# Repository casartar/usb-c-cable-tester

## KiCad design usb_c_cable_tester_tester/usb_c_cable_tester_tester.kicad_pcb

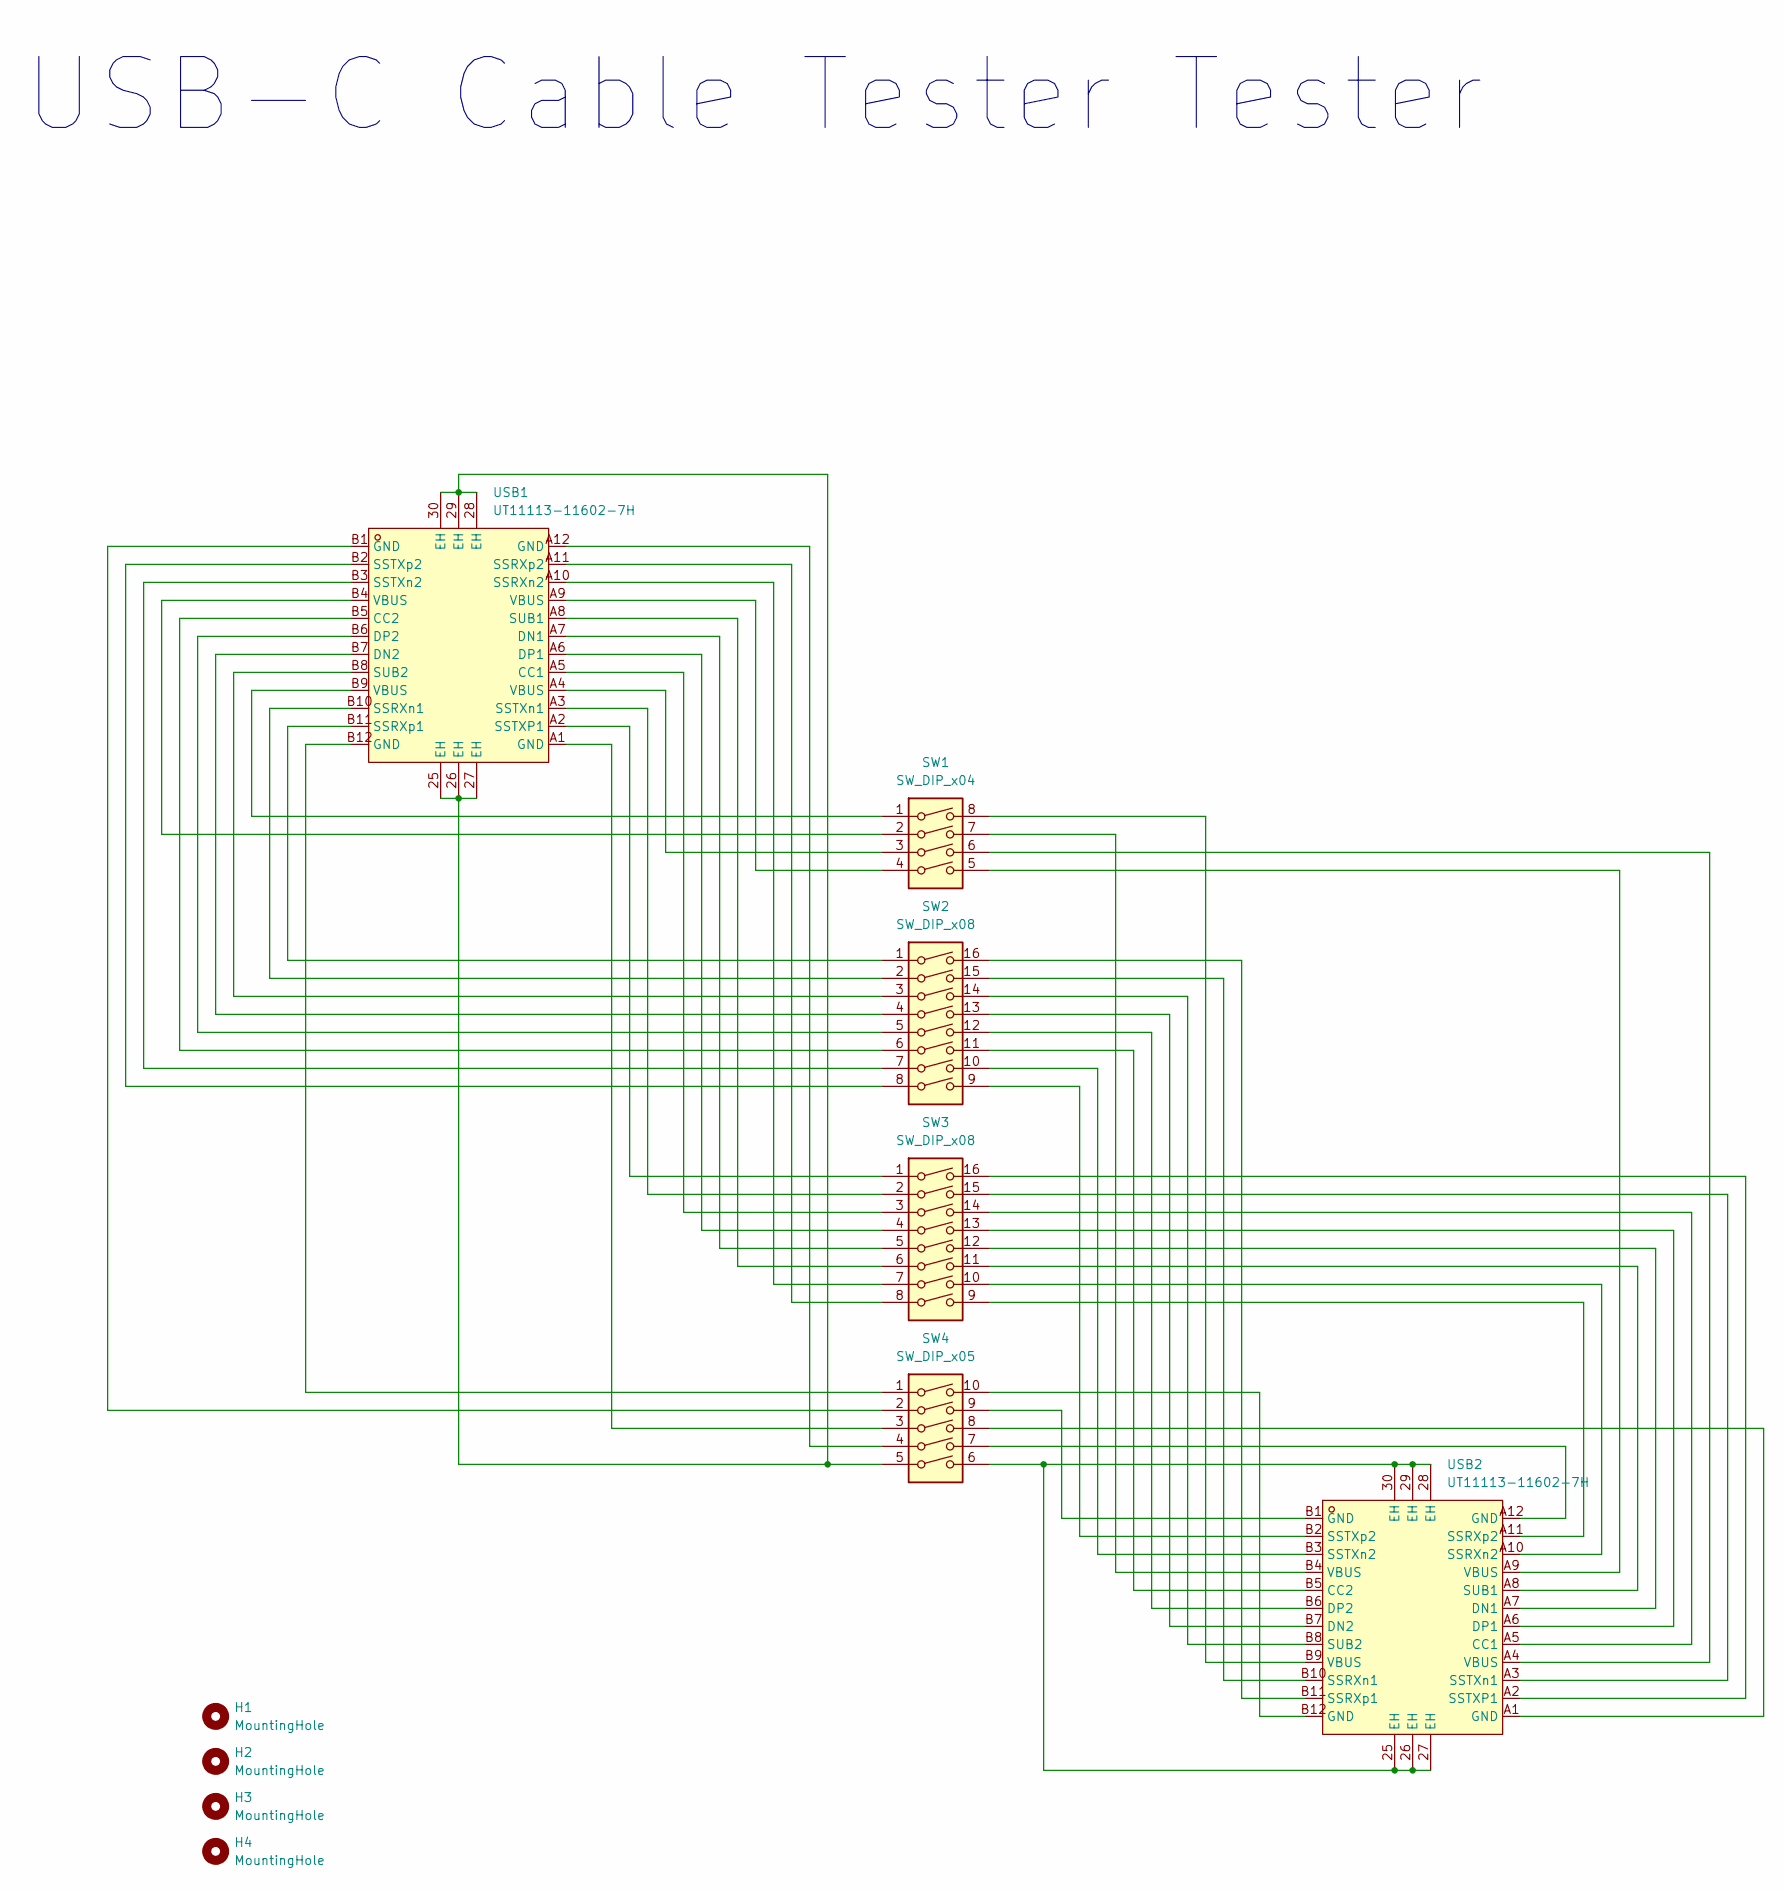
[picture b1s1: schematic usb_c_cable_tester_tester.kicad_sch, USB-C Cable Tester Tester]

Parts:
H1, H2, H3, H4: MountingHole; MountingHole_3.2mm_M3
SW1: SW_DIP_x04; SW_DIP_SPSTx04_Slide_9.78x12.34mm_W7.62mm_P2.54mm
SW2, SW3: SW_DIP_x08; SW_DIP_SPSTx08_Slide_9.78x22.5mm_W7.62mm_P2.54mm
SW4: SW_DIP_x05; SW_DIP_SPSTx05_Slide_9.78x14.88mm_W7.62mm_P2.54mm
USB1, USB2: UT11113-11602-7H; USB-C-SMD_UT11113-11602-7H; LCSC Part C2761408

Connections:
unnamed: SW1.1, USB1.B9 (VBUS)
unnamed: SW1.2, USB1.B4 (VBUS)
unnamed: SW1.3, USB1.A4 (VBUS)
unnamed: SW1.4, USB1.A9 (VBUS)
unnamed: SW1.5, USB2.A9 (VBUS)
unnamed: SW1.6, USB2.A4 (VBUS)
unnamed: SW1.7, USB2.B4 (VBUS)
unnamed: SW1.8, USB2.B9 (VBUS)
unnamed: SW4.1, USB1.B12 (GND)
unnamed: SW4.2, USB1.B1 (GND)
unnamed: SW4.3, USB1.A1 (GND)
unnamed: SW4.4, USB1.A12 (GND)
unnamed: SW4.5, USB1.25 (EH), USB1.26 (EH), USB1.27 (EH), USB1.28 (EH), USB1.29 (EH), USB1.30 (EH)
unnamed: SW4.6, USB2.25 (EH), USB2.26 (EH), USB2.27 (EH), USB2.28 (EH), USB2.29 (EH), USB2.30 (EH)
unnamed: SW4.7, USB2.A12 (GND)
unnamed: SW4.8, USB2.A1 (GND)
unnamed: SW4.9, USB2.B1 (GND)
unnamed: SW4.10, USB2.B12 (GND)
unnamed: SW3.3, USB1.A5 (CC1)
unnamed: SW2.6, USB1.B5 (CC2)
unnamed: SW3.5, USB1.A7 (DN1)
unnamed: SW2.4, USB1.B7 (DN2)
unnamed: SW3.4, USB1.A6 (DP1)
unnamed: SW2.5, USB1.B6 (DP2)
unnamed: SW2.2, USB1.B10 (SSRXn1)
unnamed: SW3.7, USB1.A10 (SSRXn2)
unnamed: SW2.1, USB1.B11 (SSRXp1)
unnamed: SW3.8, USB1.A11 (SSRXp2)
unnamed: SW3.1, USB1.A2 (SSTXP1)
unnamed: SW3.2, USB1.A3 (SSTXn1)
unnamed: SW2.7, USB1.B3 (SSTXn2)
unnamed: SW2.8, USB1.B2 (SSTXp2)
unnamed: SW3.6, USB1.A8 (SUB1)
unnamed: SW2.3, USB1.B8 (SUB2)
unnamed: SW3.14, USB2.A5 (CC1)
unnamed: SW2.11, USB2.B5 (CC2)
unnamed: SW3.12, USB2.A7 (DN1)
unnamed: SW2.13, USB2.B7 (DN2)
unnamed: SW3.13, USB2.A6 (DP1)
unnamed: SW2.12, USB2.B6 (DP2)
unnamed: SW2.15, USB2.B10 (SSRXn1)
unnamed: SW3.10, USB2.A10 (SSRXn2)
unnamed: SW2.16, USB2.B11 (SSRXp1)
unnamed: SW3.9, USB2.A11 (SSRXp2)
unnamed: SW3.16, USB2.A2 (SSTXP1)
unnamed: SW3.15, USB2.A3 (SSTXn1)
unnamed: SW2.10, USB2.B3 (SSTXn2)
unnamed: SW2.9, USB2.B2 (SSTXp2)
unnamed: SW3.11, USB2.A8 (SUB1)
unnamed: SW2.14, USB2.B8 (SUB2)

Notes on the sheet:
USB-C Cable Tester Tester

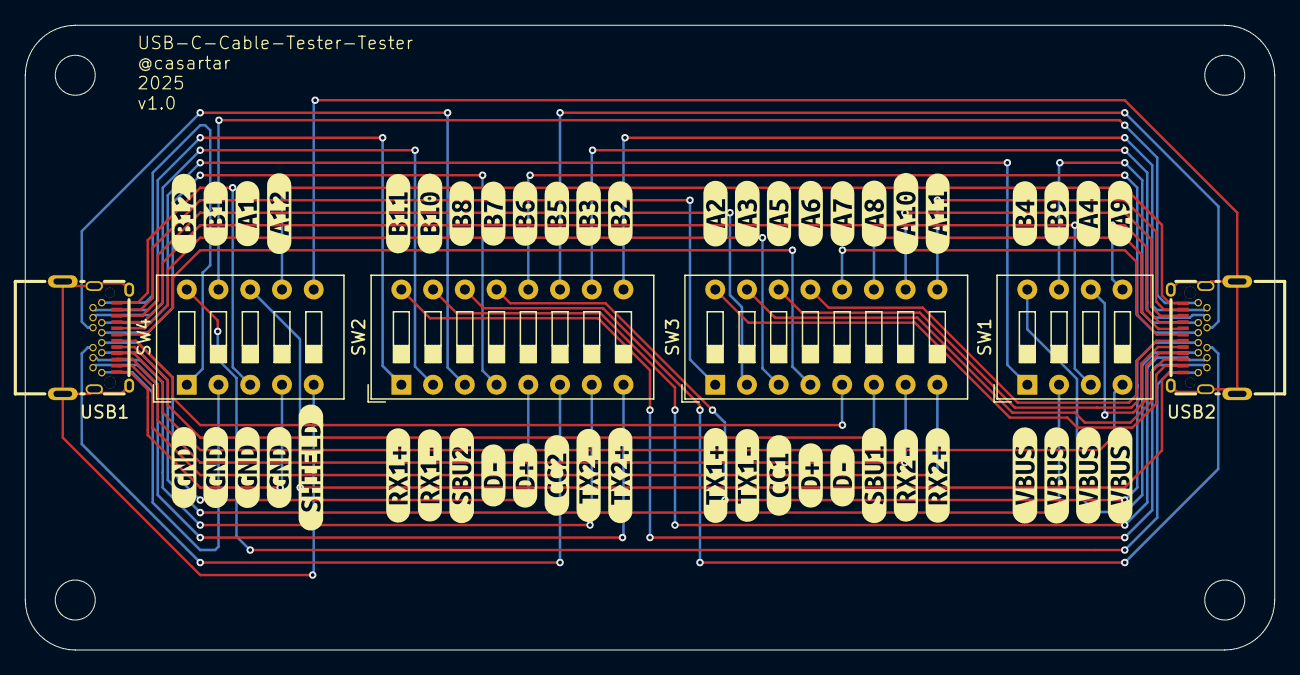
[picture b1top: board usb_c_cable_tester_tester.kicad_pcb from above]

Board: 2 copper layers, 100.0 x 50.0 mm, 59 parts (0 on the bottom side), 50 nets.

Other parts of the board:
kibuzzard-678D5F38, kibuzzard-678D5F38#2, kibuzzard-678D5F38#3, kibuzzard-678D5F38#4: G***; kibuzzard-678D5F38
kibuzzard-678D5FA3: G***; kibuzzard-678D5FA3
kibuzzard-678D5FC4: G***; kibuzzard-678D5FC4
kibuzzard-678D5FDE: G***; kibuzzard-678D5FDE
kibuzzard-678D5FEA, kibuzzard-678D5FEA#2, kibuzzard-678D5FEA#3, kibuzzard-678D5FEA#4: G***; kibuzzard-678D5FEA
kibuzzard-678D6F6F: G***; kibuzzard-678D6F6F
kibuzzard-678D6F8E: G***; kibuzzard-678D6F8E
kibuzzard-678D6F9D: G***; kibuzzard-678D6F9D
kibuzzard-678D6F82: G***; kibuzzard-678D6F82
kibuzzard-678D6FAB: G***; kibuzzard-678D6FAB
kibuzzard-678D6FB9: G***; kibuzzard-678D6FB9
kibuzzard-678D6FD7: G***; kibuzzard-678D6FD7
kibuzzard-678D6FE6: G***; kibuzzard-678D6FE6
kibuzzard-678D56BE: G***; kibuzzard-678D56BE
kibuzzard-678D56C4: G***; kibuzzard-678D56C4
kibuzzard-678D56CC: G***; kibuzzard-678D56CC
kibuzzard-678D56D1: G***; kibuzzard-678D56D1
kibuzzard-678D56D6: G***; kibuzzard-678D56D6
kibuzzard-678D56DC: G***; kibuzzard-678D56DC
kibuzzard-678D56E1: G***; kibuzzard-678D56E1
kibuzzard-678D56E7: G***; kibuzzard-678D56E7
kibuzzard-678D56EC: G***; kibuzzard-678D56EC
kibuzzard-678D56F1: G***; kibuzzard-678D56F1
kibuzzard-678D569F: G***; kibuzzard-678D569F
kibuzzard-678D571B: G***; kibuzzard-678D571B
kibuzzard-678D572A: G***; kibuzzard-678D572A
kibuzzard-678D572F: G***; kibuzzard-678D572F
kibuzzard-678D573D: G***; kibuzzard-678D573D
kibuzzard-678D700A: G***; kibuzzard-678D700A
kibuzzard-678D704B: G***; kibuzzard-678D704B
kibuzzard-678D5650: G***; kibuzzard-678D5650
kibuzzard-678D5711: G***; kibuzzard-678D5711
kibuzzard-678D5716: G***; kibuzzard-678D5716
kibuzzard-678D5720: G***; kibuzzard-678D5720
kibuzzard-678D5725: G***; kibuzzard-678D5725
kibuzzard-678D5733: G***; kibuzzard-678D5733
kibuzzard-678D5738: G***; kibuzzard-678D5738
kibuzzard-678D5742: G***; kibuzzard-678D5742
kibuzzard-678D5747: G***; kibuzzard-678D5747
kibuzzard-678D7016: G***; kibuzzard-678D7016
kibuzzard-678D7021: G***; kibuzzard-678D7021
kibuzzard-678D7031: G***; kibuzzard-678D7031
kibuzzard-678D7040: G***; kibuzzard-678D7040

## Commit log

2025-01-19 first layout
2025-01-19 layout finished
